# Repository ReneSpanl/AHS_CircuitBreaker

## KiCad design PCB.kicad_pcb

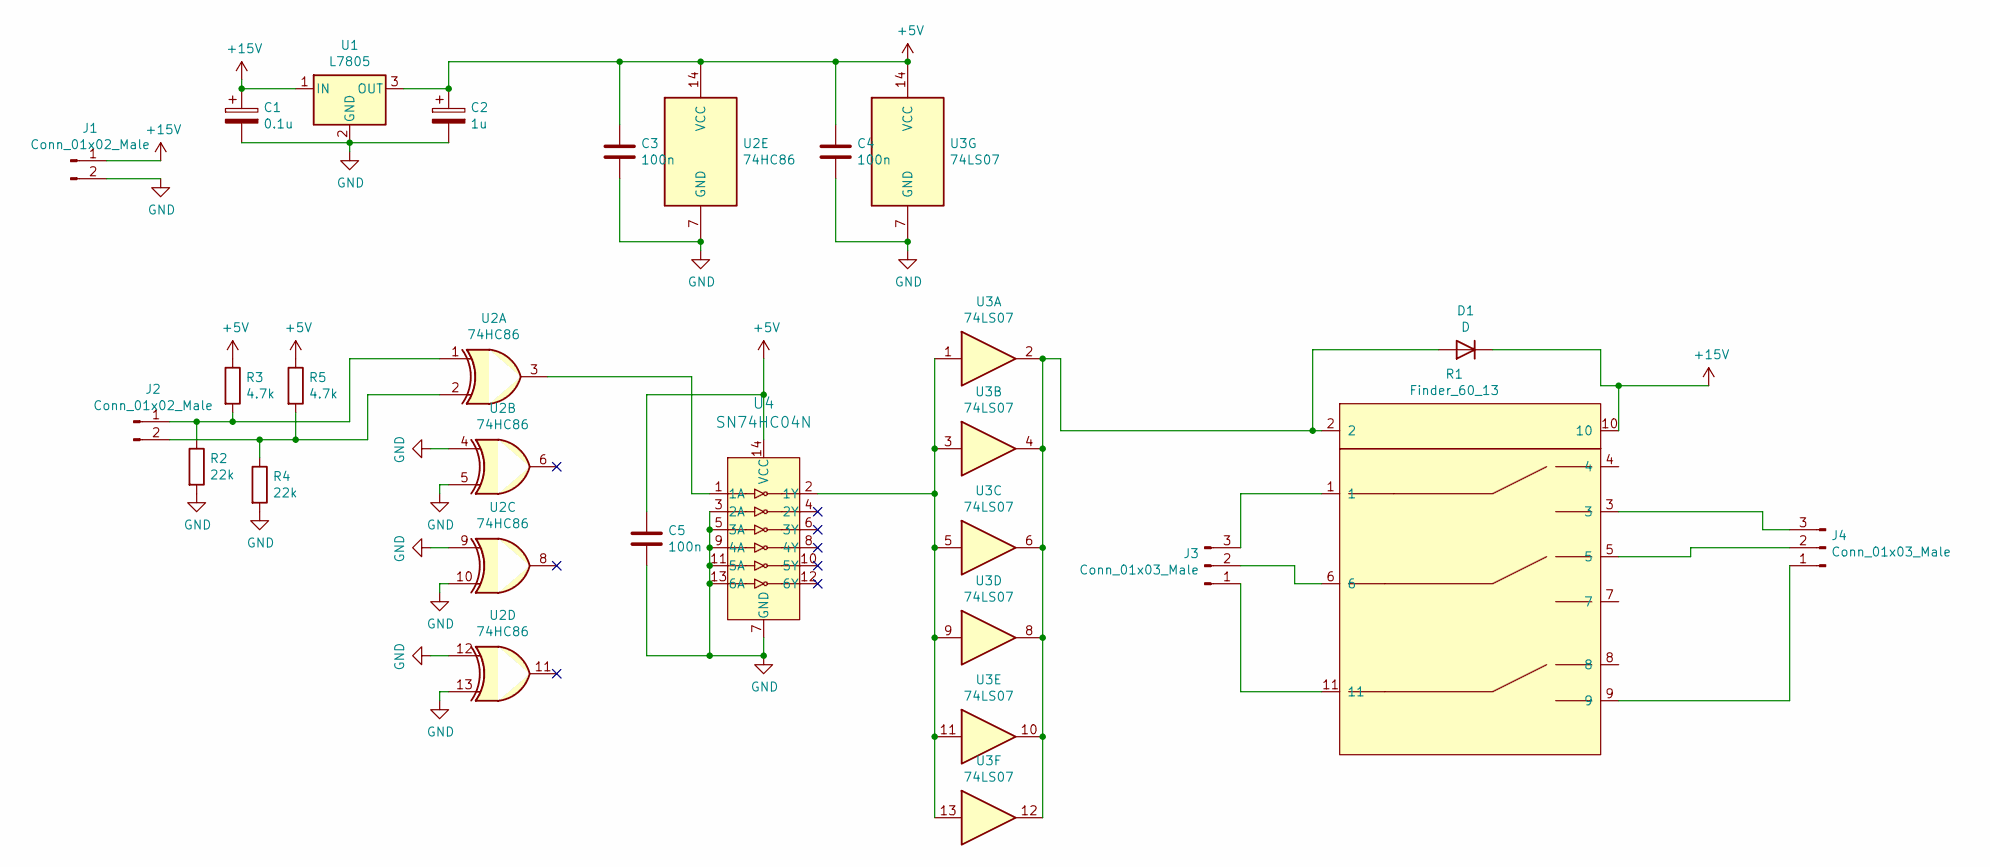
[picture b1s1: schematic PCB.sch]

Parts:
C1: 0.1u; CP_Radial_D5.0mm_P2.00mm
C2: 1u; CP_Radial_D5.0mm_P2.00mm
C3, C4, C5: 100n; C_Disc_D3.4mm_W2.1mm_P2.50mm
D1: D; D_DO-41_SOD81_P10.16mm_Horizontal
J1, J2: Conn_01x02_Male; CONNECTOR 5.08
J3, J4: Conn_01x03_Male; 3_Pin_4mm_Laborstecker_Schutzkontakte
R1: Finder_60_13; Finder60.13NEU
R2, R4: 22k; R_Axial_DIN0207_L6.3mm_D2.5mm_P10.16mm_Horizontal
R3, R5: 4.7k; R_Axial_DIN0207_L6.3mm_D2.5mm_P10.16mm_Horizontal
U1: L7805; TO-220-3_Vertical
U2: 74HC86; DIP-14_W7.62mm
U3: 74LS07; DIP-14_W7.62mm
U4: SN74HC04N; DIP-14_W7.62mm_LongPads; MPN SN74HC04N; Digi-Key_PN 296-1566-5-ND

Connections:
+5V: C2.1, C3.1, C4.1, C5.1, R3.1, R5.1, U1.3 (OUT), U2.14 (VCC), U3.14 (VCC), U4.14 (VCC)
+15V: C1.1, D1.1 (K), J1.1, R1.10, U1.1 (IN)
GND: C1.2, C2.2, C3.2, C4.2, C5.2, J1.2, R2.2, R4.2, U1.2 (GND), U2.4, U2.5, U2.7 (GND), U2.9, U2.10, U2.12, U2.13, U3.7 (GND), U4.3 (2A), U4.5 (3A), U4.7 (GND), U4.9 (4A), U4.11 (5A), U4.13 (6A)
unnamed: D1.2 (A), R1.2, U3.2, U3.4, U3.6, U3.8, U3.10, U3.12
unnamed: J2.1, R2.1, R3.2, U2.1
unnamed: J2.2, R4.1, R5.2, U2.2
unnamed: J3.1, R1.11
unnamed: J3.2, R1.6
unnamed: J3.3, R1.1
unnamed: J4.1, R1.9
unnamed: J4.2, R1.5
unnamed: J4.3, R1.3
unnamed: U2.3, U4.1 (1A)
unnamed: U3.1, U3.3, U3.5, U3.9, U3.11, U3.13, U4.2 (1Y)

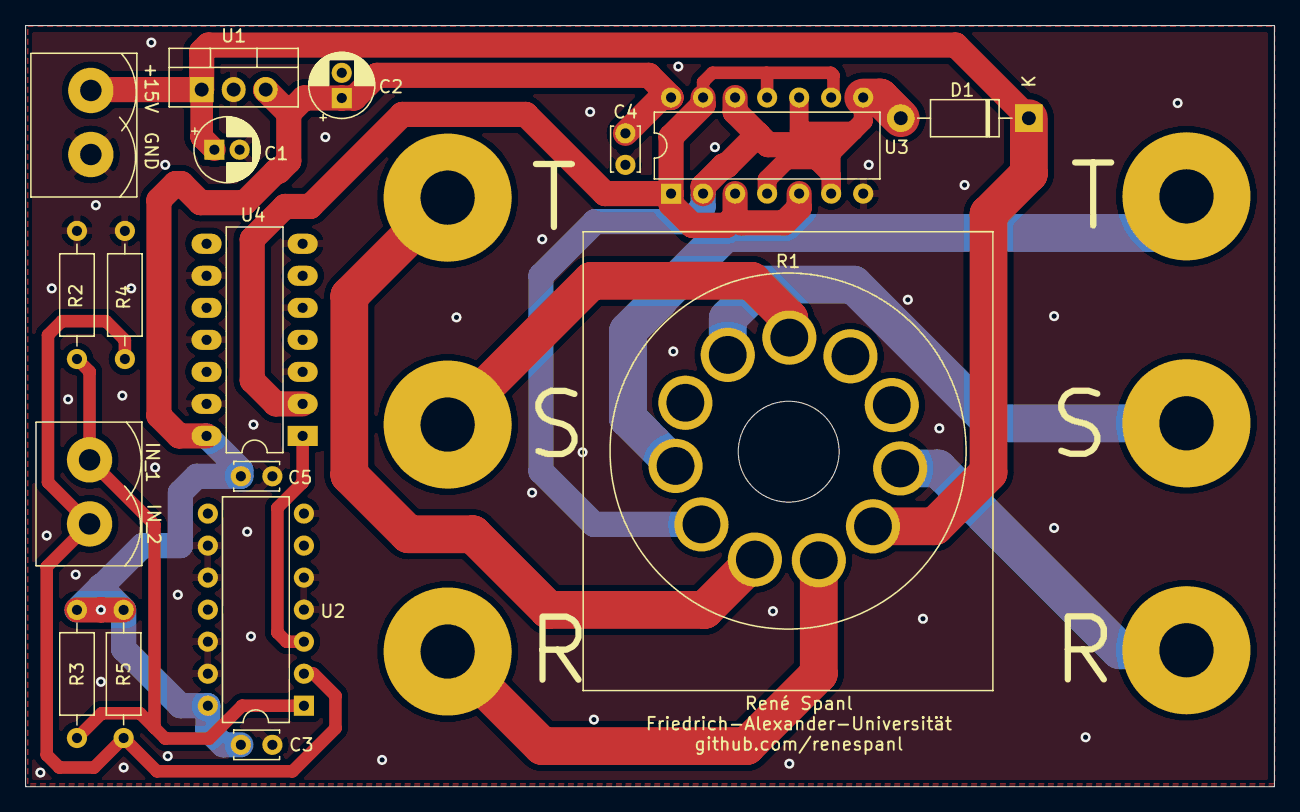
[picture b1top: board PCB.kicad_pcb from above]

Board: 2 copper layers, 99.1 x 60.4 mm, 19 parts (0 on the bottom side), 14 nets.

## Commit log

2021-05-28 Final Revision
    Maybe there are Resistors needed
